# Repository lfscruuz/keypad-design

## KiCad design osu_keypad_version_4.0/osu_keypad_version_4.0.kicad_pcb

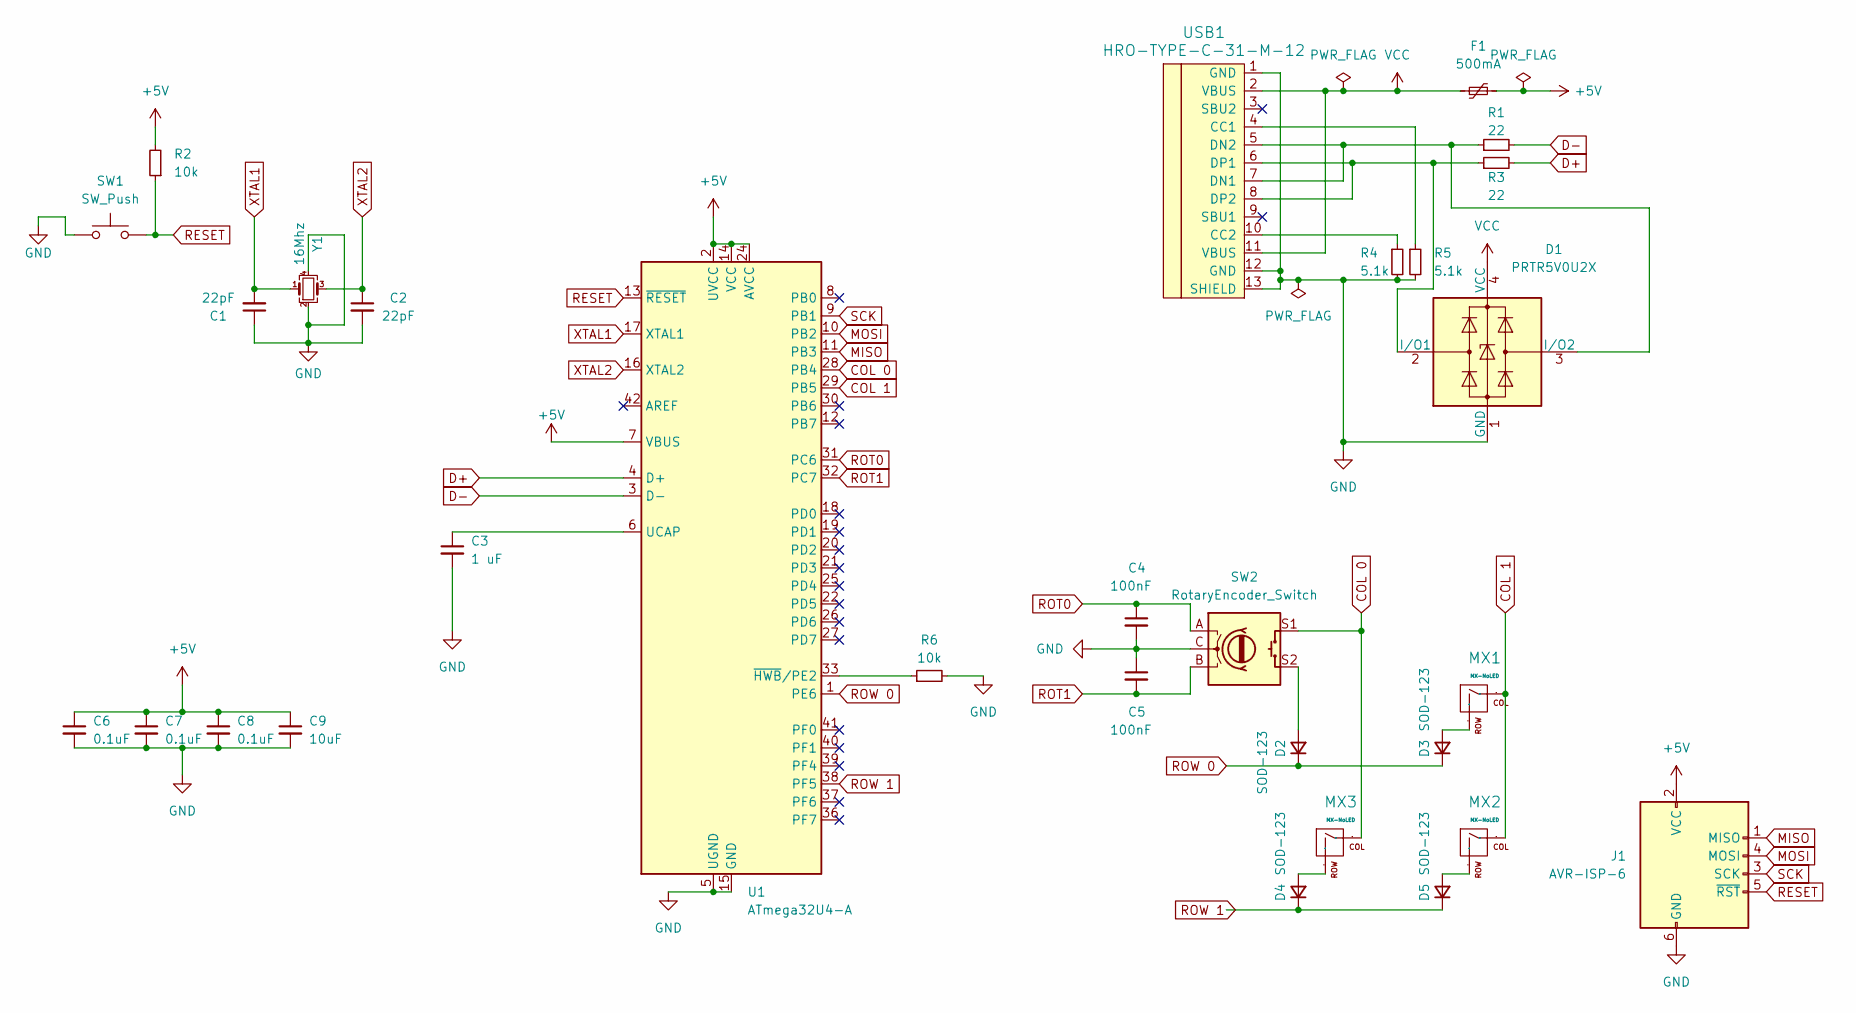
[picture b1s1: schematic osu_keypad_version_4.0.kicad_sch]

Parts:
C1, C2: 22pF; C_0805_2012Metric_Pad1.18x1.45mm_HandSolder
C3: 1 uF; C_0805_2012Metric_Pad1.18x1.45mm_HandSolder
C4, C5: 100nF; C_0805_2012Metric_Pad1.18x1.45mm_HandSolder
C6, C7, C8: 0.1uF; C_0805_2012Metric_Pad1.18x1.45mm_HandSolder
C9: 10uF; C_0805_2012Metric_Pad1.18x1.45mm_HandSolder
D1: PRTR5V0U2X; SOT143B
D2, D3, D4, D5: SOD-123; D_SOD-123
F1: 500mA; Fuse_1206_3216Metric_Pad1.42x1.75mm_HandSolder
J1: AVR-ISP-6; Reset_Pretty-Mask
MX1, MX2, MX3: MX-NoLED; ALPS-1U
R1, R3: 22; R_0805_2012Metric_Pad1.20x1.40mm_HandSolder
R2: 10k; R_0805_2012Metric_Pad1.20x1.40mm_HandSolder
R4, R5: 5.1k; R_0805_2012Metric_Pad1.20x1.40mm_HandSolder
R6: 10k; R_0805_2012Metric
SW1: SW_Push; SW_SPST_SKQG_WithStem
SW2: RotaryEncoder_Switch; RotaryEncoder_Alps_EC12E-Switch_Vertical_H20mm
U1: ATmega32U4-A; TQFP-44_10x10mm_P0.8mm
USB1: HRO-TYPE-C-31-M-12; HRO-TYPE-C-31-M-12-HandSoldering
Y1: 16Mhz; Crystal_SMD_3225-4Pin_3.2x2.5mm_HandSoldering

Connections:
+5V: C6.1, C7.1, C8.1, C9.1, F1.2, J1.2 (VCC), R2.2, U1.2 (UVCC), U1.7 (VBUS), U1.14 (VCC), U1.24 (AVCC), U1.34 (VCC), U1.44 (AVCC)
COL 0: MX3.1 (COL), SW2.S1, U1.28 (PB4)
COL 1: MX1.1 (COL), MX2.1 (COL), U1.29 (PB5)
D+: R3.2, U1.4 (D+)
D-: R1.2, U1.3 (D-)
GND: C1.1, C2.2, C3.2, C4.2, C5.1, C6.2, C7.2, C8.2, C9.2, D1.1 (GND), J1.6 (GND), R4.2, R5.2, R6.2, SW1.1, SW2.C, U1.5 (UGND), U1.15 (GND), U1.23 (GND), U1.35 (GND), U1.43 (GND), USB1.1 (GND), USB1.12 (GND), USB1.13 (SHIELD), Y1.2, Y1.4
MISO: J1.1 (MISO), U1.11 (PB3)
MOSI: J1.4 (MOSI), U1.10 (PB2)
unnamed: D1.2 (I/O1), R3.1, USB1.6 (DP1), USB1.8 (DP2)
unnamed: D1.3 (I/O2), R1.1, USB1.5 (DN2), USB1.7 (DN1)
unnamed: D2.2 (A), SW2.S2
unnamed: D3.2 (A), MX1.2 (ROW)
unnamed: D4.2 (A), MX3.2 (ROW)
unnamed: D5.2 (A), MX2.2 (ROW)
unnamed: C3.1, U1.6 (UCAP)
unnamed: R6.1, U1.33 (~HWB/PE2)
unnamed: R5.1, USB1.4 (CC1)
unnamed: R4.1, USB1.10 (CC2)
RESET: J1.5 (~RST), R2.1, SW1.2, U1.13 (~RESET)
ROT0: C4.1, SW2.A, U1.31 (PC6)
ROT1: C5.2, SW2.B, U1.32 (PC7)
ROW 0: D2.1 (K), D3.1 (K), U1.1 (PE6)
ROW 1: D4.1 (K), D5.1 (K), U1.38 (PF5)
SCK: J1.3 (SCK), U1.9 (PB1)
VCC: D1.4 (VCC), F1.1, USB1.2 (VBUS), USB1.11 (VBUS)
XTAL1: C1.2, U1.17 (XTAL1), Y1.1
XTAL2: C2.1, U1.16 (XTAL2), Y1.3

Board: 2 copper layers, 30 parts (30 on the bottom side), 27 nets, no tracks yet.

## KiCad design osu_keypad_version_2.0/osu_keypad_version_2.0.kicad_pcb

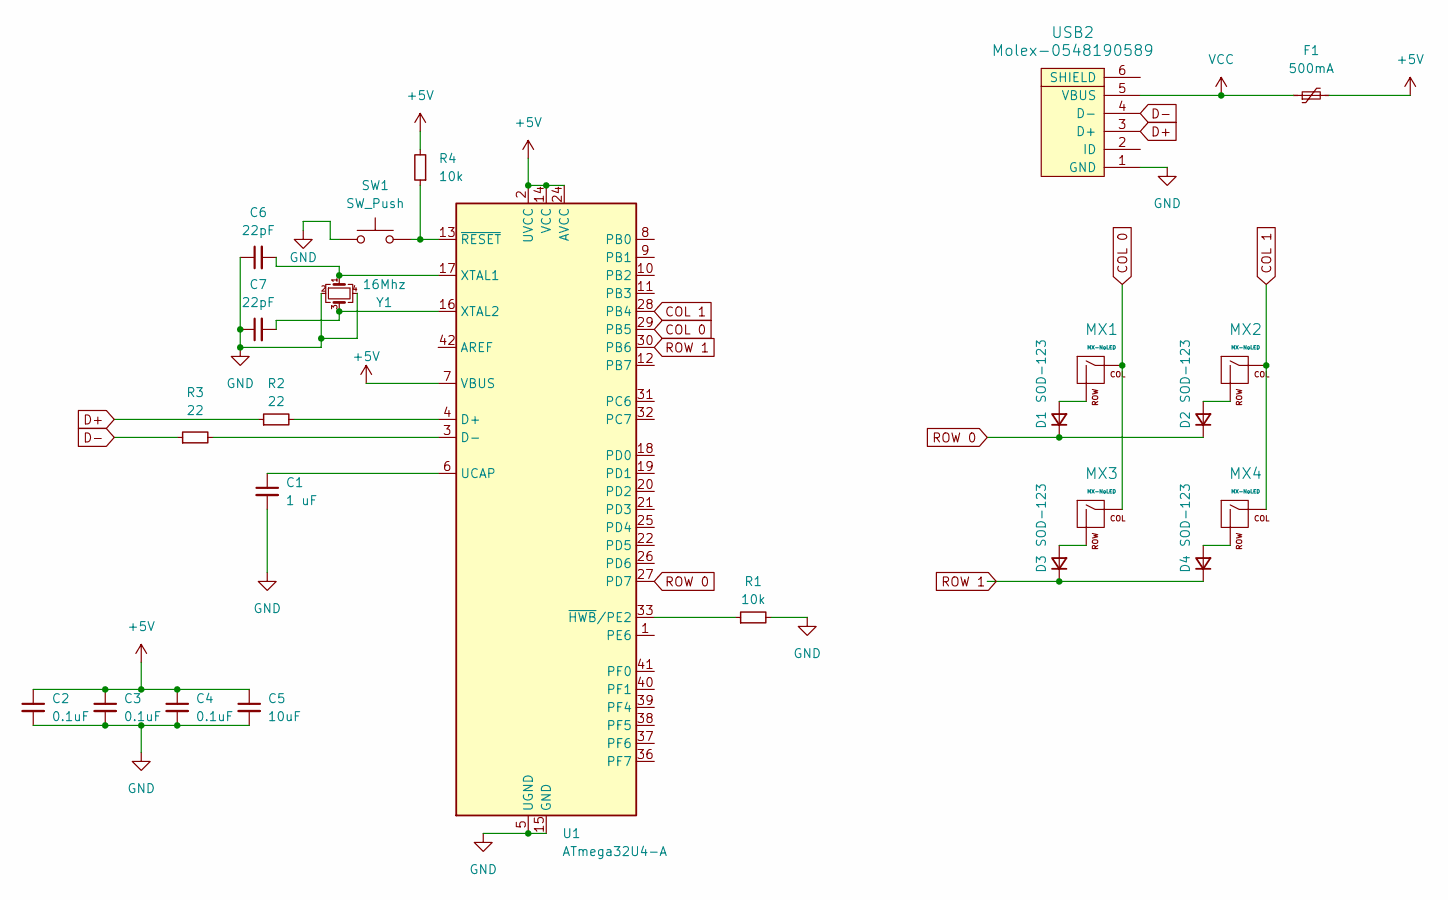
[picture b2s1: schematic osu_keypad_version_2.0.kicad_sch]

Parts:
C1: 1 uF; C_0805_2012Metric
C2, C3, C4: 0.1uF; C_0805_2012Metric
C5: 10uF; C_0805_2012Metric
C6, C7: 22pF; C_0805_2012Metric
D1, D2, D3, D4: SOD-123; D_SOD-123
F1: 500mA; Fuse_1206_3216Metric
MX1, MX2, MX3, MX4: MX-NoLED; MX-1U-NoLED
R1, R4: 10k; R_0805_2012Metric
R2, R3: 22; R_0805_2012Metric
SW1: SW_Push; SKQG-1155865
U1: ATmega32U4-A; TQFP-44_10x10mm_P0.8mm
USB2: Molex-0548190589
Y1: 16Mhz; Crystal_SMD_3225-4Pin_3.2x2.5mm

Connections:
+5V: C2.1, C3.1, C4.1, C5.1, F1.2, R4.2, U1.2 (UVCC), U1.7 (VBUS), U1.14 (VCC), U1.24 (AVCC), U1.34 (VCC), U1.44 (AVCC)
COL 0: MX1.1 (COL), MX3.1 (COL), U1.29 (PB5)
COL 1: MX2.1 (COL), MX4.1 (COL), U1.28 (PB4)
D+: R2.1, USB2.3 (D+)
D-: R3.1, USB2.4 (D-)
GND: C1.2, C2.2, C3.2, C4.2, C5.2, C6.1, C7.1, R1.2, SW1.1, U1.5 (UGND), U1.15 (GND), U1.23 (GND), U1.35 (GND), U1.43 (GND), USB2.1 (GND), Y1.2, Y1.4
unnamed: D1.2 (A), MX1.2 (ROW)
unnamed: D2.2 (A), MX2.2 (ROW)
unnamed: D3.2 (A), MX3.2 (ROW)
unnamed: D4.2 (A), MX4.2 (ROW)
unnamed: R2.2, U1.4 (D+)
unnamed: R3.2, U1.3 (D-)
unnamed: C1.1, U1.6 (UCAP)
unnamed: C6.2, U1.17 (XTAL1), Y1.1
unnamed: C7.2, U1.16 (XTAL2), Y1.3
unnamed: R1.1, U1.33 (~HWB/PE2)
unnamed: R4.1, SW1.2, U1.13 (~RESET)
ROW 0: D1.1 (K), D2.1 (K), U1.27 (PD7)
ROW 1: D3.1 (K), D4.1 (K), U1.30 (PB6)
VCC: F1.1, USB2.5 (VBUS)

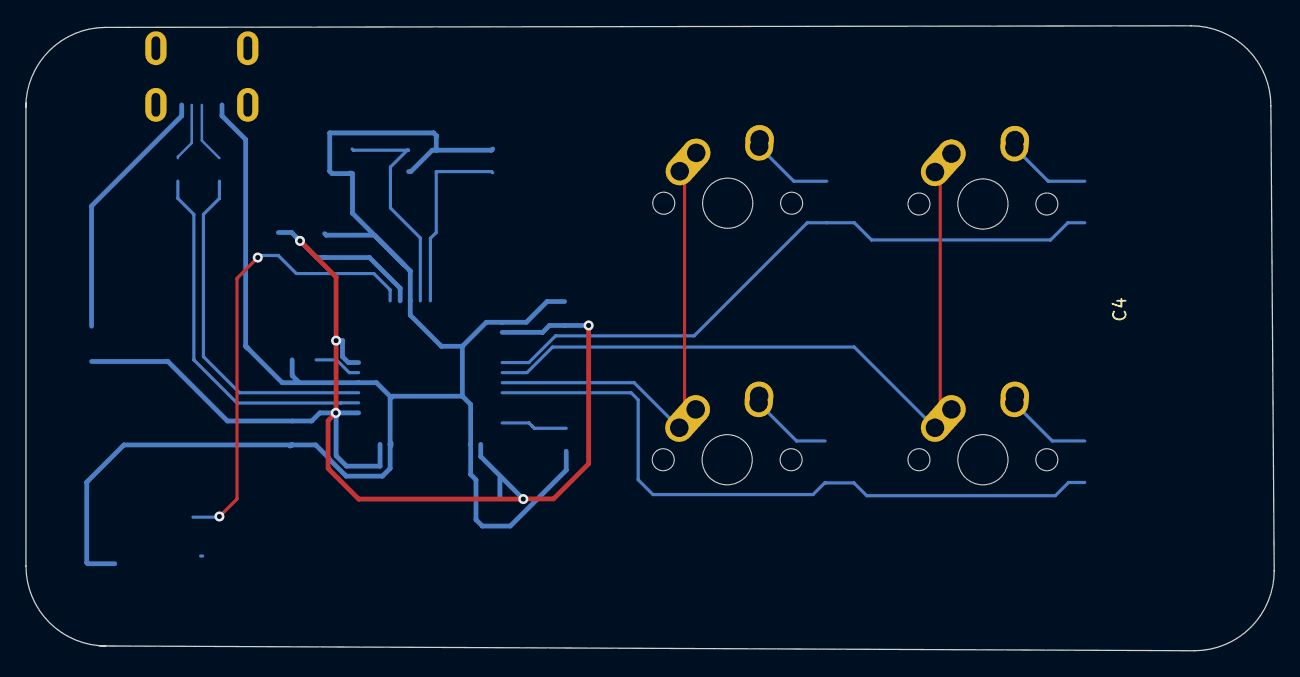
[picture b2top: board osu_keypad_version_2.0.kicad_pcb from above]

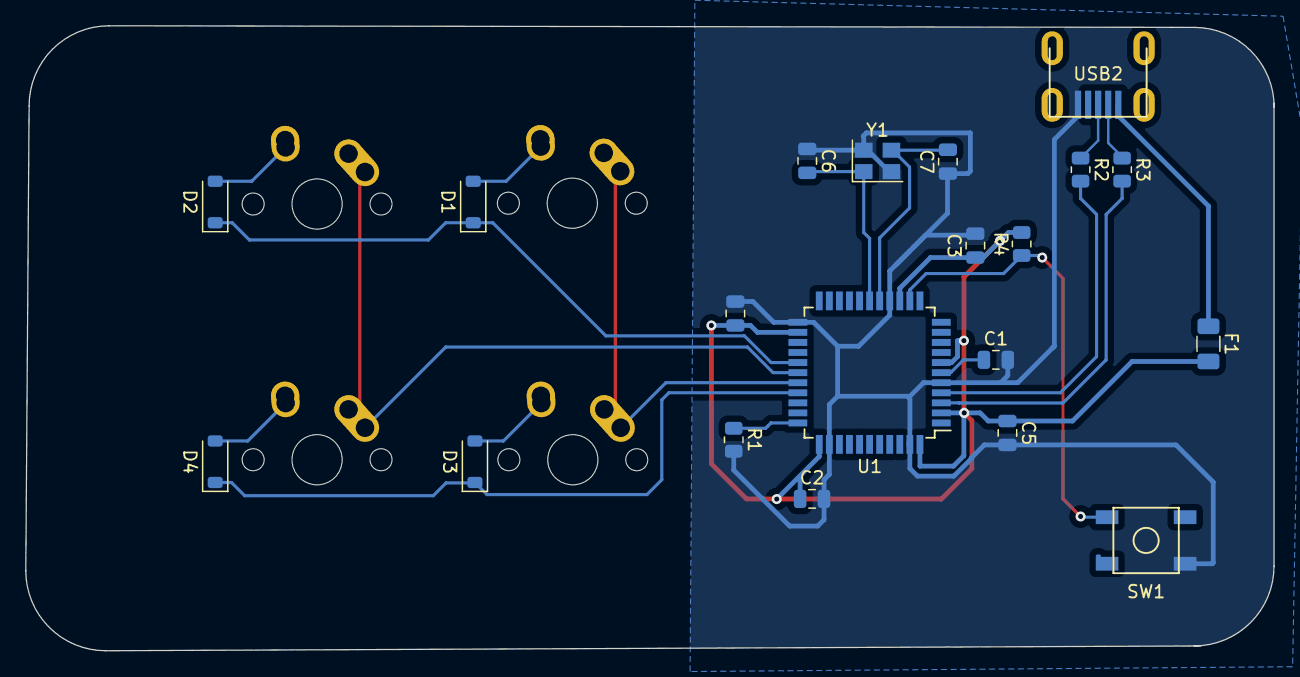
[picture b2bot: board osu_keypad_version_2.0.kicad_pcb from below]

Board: 2 copper layers, 99.2 x 49.7 mm, 24 parts (20 on the bottom side), 20 nets.

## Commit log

2024-01-31 project initialized
2024-01-31 libraries added
2024-01-31 libraries relocated
2024-01-31 libraries set up
2024-02-18 downgraded kicad version, new project created
2024-02-18 installed libs
2024-02-24 changed to the atmega32u4, finished mcu schema
2024-02-24 finished part 4 of ai03's guide
2024-02-25 routing done
2024-02-25 added safe zone
2024-03-03 readded submodules
2024-03-03 v3 created
2024-03-03 old ver 2
2024-03-03 moved submodules to their own folder
2024-03-03 retried moving submodules
2024-03-03 usbc submodule added
2024-03-04 isp symbol added
2024-03-09 wired usbc
2024-10-17 v4 initialized
2024-10-22 added rotary encoder
2024-10-29 update submodules
2024-10-31 added footprints
2024-10-31 started arranging the footprints
